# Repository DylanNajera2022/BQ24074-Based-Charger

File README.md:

# BQ24074-Based-Charger
I wanted a lithium battery charging module, but I felt that simply buying one wouldn't be fun. So I decided to create my own module from scratch. First, I researched a bit about which chip would be best for me and decided to go with the BQ24074 for its simplicity and small size. I based it on the Texas Instruments datasheet to create it. I decided to set it to USB500 mode because if I set it to the 1.2A fast charge mode, it would get too hot and I feel like I would never use that.Here are some pictures of my schematic and my PCB:

My goal with this module was to make it as compact as possible. I wanted to make a PCB with components on both sides, but that would have increased the cost too much to have it made with JLCPB. I would like to solder it myself, but the problem is that to solder the chip I would need a heat gun or a hot plate, neither of which I have. So I ended up with this, which is the simplest option.

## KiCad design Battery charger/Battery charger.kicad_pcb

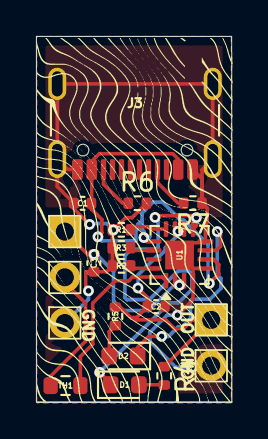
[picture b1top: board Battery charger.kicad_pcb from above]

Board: 2 copper layers, 10.8 x 20.3 mm, 17 parts (0 on the bottom side), 15 nets.

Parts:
C1, C2, C3: 10uF; C_0402_1005Metric
D1, D2: LED; LED_0603_1608Metric
J1: Conn_01x02_Pin; PinHeader_1x02_P2.54mm_Vertical
J2: Conn_01x03_Pin; PinHeader_1x03_P2.54mm_Vertical
J3: USB_C_Receptacle_USB2.0_14P; USB_C_Receptacle_GCT_USB4105-xx-A_16P_TopMnt_Horizontal
R1: 1.62k; R_0402_1005Metric
R2: 750; R_0402_1005Metric
R3: 49.9K; R_0402_1005Metric
R4, R5: 1.5K; R_0402_1005Metric
R6, R7: 5.1k; R_0402_1005Metric
TH1: Thermistor_NTC; R_0603_1608Metric
U1: BQ24074RGT; VQFN-16-1EP_3x3mm_P0.5mm_EP1.6x1.6mm

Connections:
GND: C1.2, C2.2, C3.2, J1.2, J2.3, J3.A1 (GND), J3.A12 (GND), J3.B1 (GND), J3.B12 (GND), J3.S1 (SHIELD), R1.2, R2.2, R3.2, R6.2, R7.1, U1.4 (~CE), U1.5 (EN2), U1.8 (VSS), U1.17 (VSS)
IN: C1.1, J3.A4 (VBUS), J3.A9 (VBUS), J3.B4 (VBUS), J3.B9 (VBUS), U1.6 (EN1), U1.13 (IN)
unnamed: D1.2 (A), R4.2
unnamed: D1.1 (K), U1.9 (~CHG)
unnamed: D2.2 (A), R5.2
unnamed: D2.1 (K), U1.7 (~PGOOD)
unnamed: C3.1, J2.1, U1.2 (BAT), U1.3 (BAT)
unnamed: J2.2, TH1.2
unnamed: J3.A5 (CC1), R7.2
unnamed: J3.B5 (CC2), R6.1
unnamed: R1.1, U1.12 (ILIM)
unnamed: R2.1, U1.16 (ISET)
unnamed: R3.1, U1.14 (TMR)
OUT: C2.1, J1.1, R4.1, R5.1, U1.10 (OUT), U1.11 (OUT)
TS: TH1.1, U1.1 (TS)

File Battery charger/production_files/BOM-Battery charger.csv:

Comment,Designator,Footprint,LCSC,Quantity
USB_C_Receptacle_USB2.0_14P,J3,USB_C_Receptacle_GCT_USB4105-xx-A_16P_TopMnt_Horizontal,,1
LED,D1,LED_0603_1608Metric,,1
10uF,C1,C_0603_1608Metric,,1
BQ24074RGT,U1,VQFN-16-1EP_3x3mm_P0.5mm_EP1.6x1.6mm,,1
Thermistor_NTC,TH1,R_0603_1608Metric,,1
5.1k,R7,R_0603_1608Metric,,1
5.1k,R6,R_0603_1608Metric,,1
1.5K,R5,R_0603_1608Metric,,1
1.5K,R4,R_0603_1608Metric,,1
49.9K,R3,R_0603_1608Metric,,1
750,R2,R_0603_1608Metric,,1
1.62k,R1,R_0603_1608Metric,,1
Conn_01x03_Pin,J2,"PhoenixContact_MC_1,5_3-G-3.5_1x03_P3.50mm_Horizontal",,1
LED,D2,LED_0603_1608Metric,,1
10uF,C3,C_0603_1608Metric,,1
10uF,C2,C_0603_1608Metric,,1

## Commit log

2026-02-25 Enhance README with detailed project background
    Expanded project description with personal insights and images.
2026-02-25 Enhance README with project details and challenges
    Added additional details about the lithium battery charging module project, including design considerations and challenges faced during PCB creation.
2026-02-25 Update README with new image of charging module
    Added an additional image to the README to showcase the module design.
2026-02-27 Update README with more schematic and PCB images
    Added additional images to the README for better visualization of the project.
